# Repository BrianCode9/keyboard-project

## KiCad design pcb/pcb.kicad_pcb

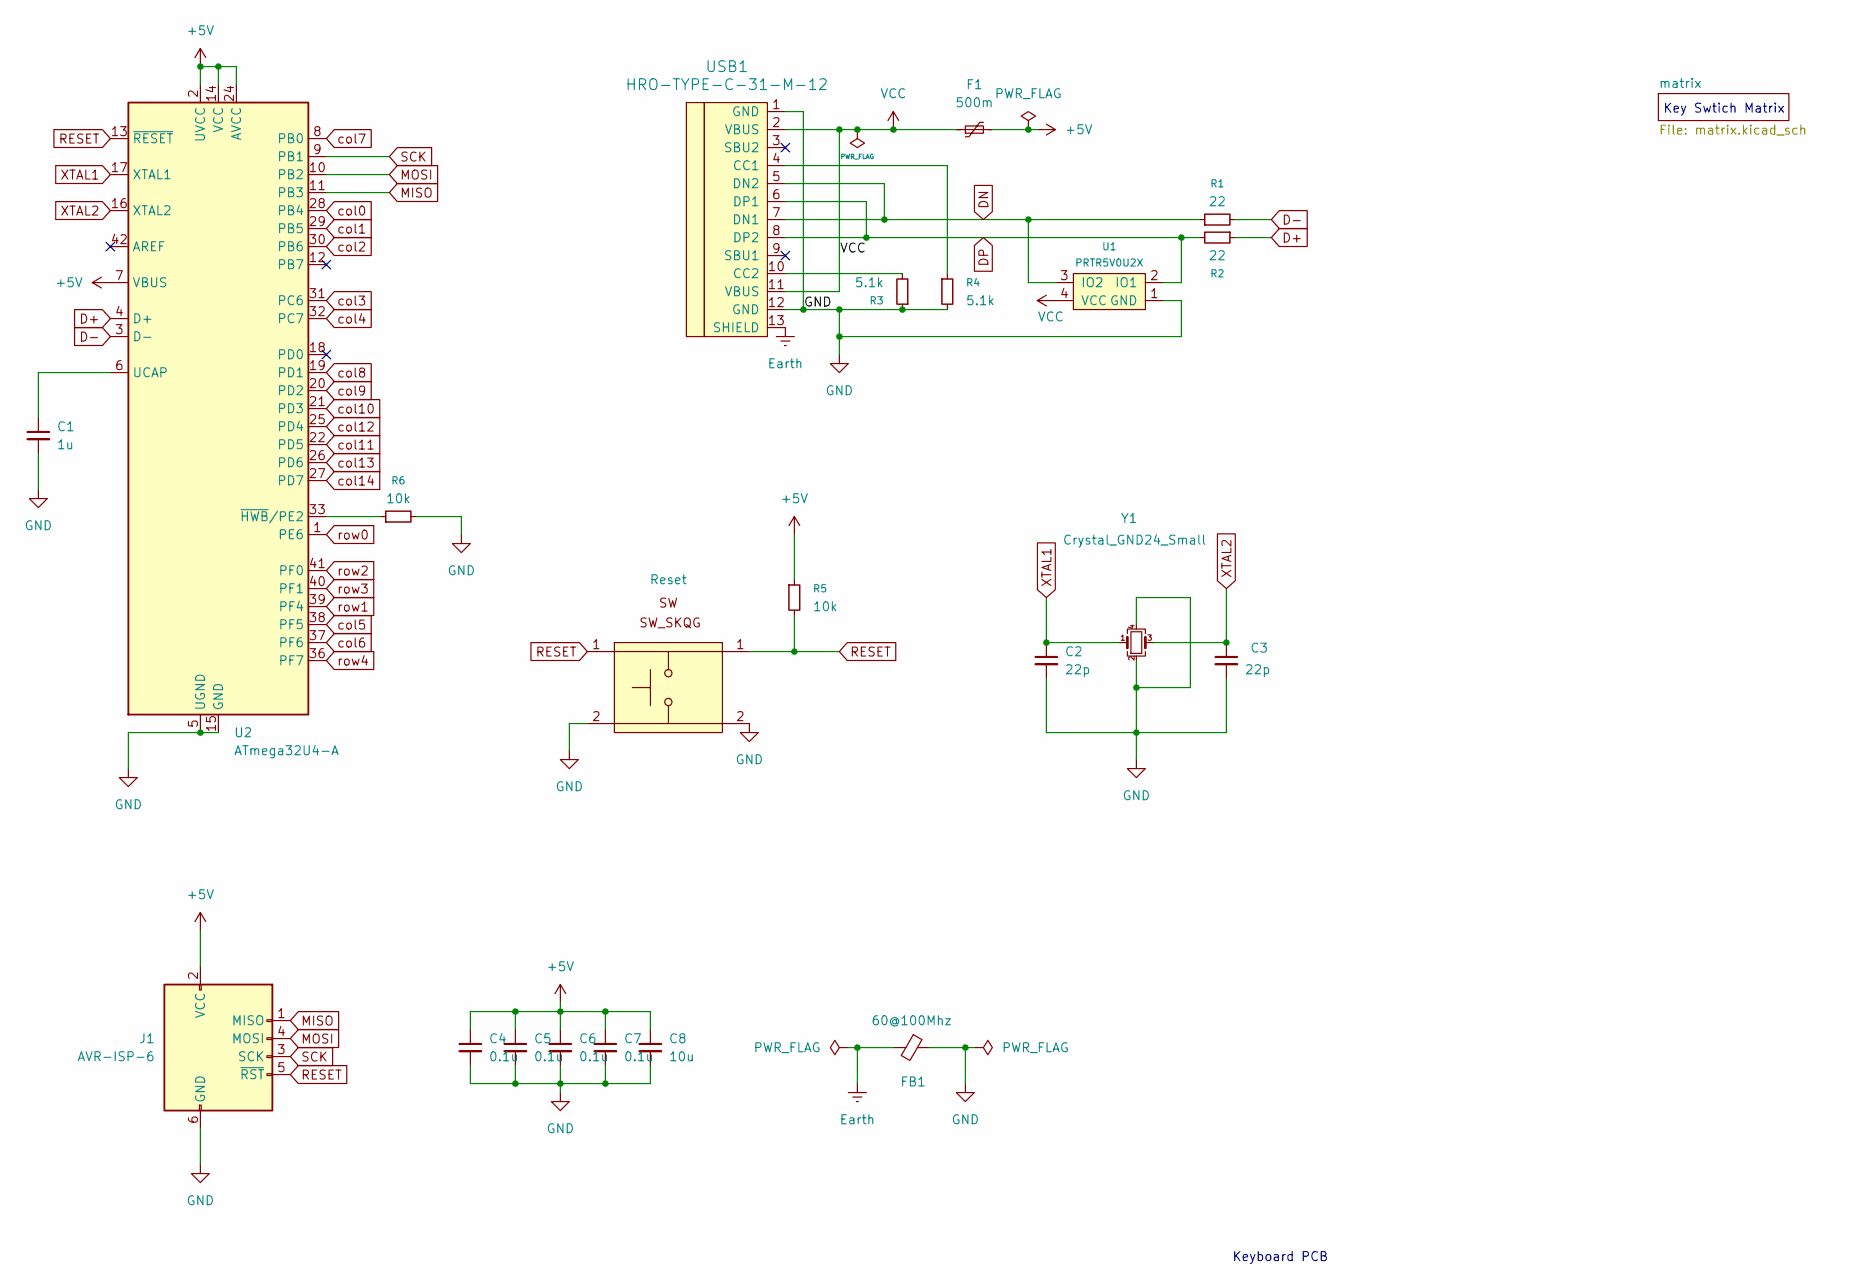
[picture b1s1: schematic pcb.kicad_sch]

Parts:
C1: 1u; C_0805_2012Metric_Pad1.18x1.45mm_HandSolder
C2, C3: 22p; C_0805_2012Metric_Pad1.18x1.45mm_HandSolder
C4, C5, C6, C7: 0.1u; C_0805_2012Metric_Pad1.18x1.45mm_HandSolder
C8: 10u; C_0805_2012Metric_Pad1.18x1.45mm_HandSolder
F1: 500m; Fuse_1206_3216Metric_Pad1.42x1.75mm_HandSolder
FB1: 60@100Mhz; L_0805_2012Metric_Pad1.05x1.20mm_HandSolder
J1: AVR-ISP-6; Reset_Pretty-Mask
R1, R2: 22; R_0805_2012Metric_Pad1.20x1.40mm_HandSolder
R3, R4: 5.1k; R_0805_2012Metric_Pad1.20x1.40mm_HandSolder
R5, R6: 10k; R_0805_2012Metric_Pad1.20x1.40mm_HandSolder
SW_RST1: Reset; SW_SPST_SKQG_WithStem
U1: PRTR5V0U2X; SOT143B
U2: ATmega32U4-A; TQFP-44_10x10mm_P0.8mm
USB1: HRO-TYPE-C-31-M-12; HRO-TYPE-C-31-M-12-HandSoldering
Y1: Crystal_GND24_Small; Crystal_SMD_3225-4Pin_3.2x2.5mm_HandSoldering

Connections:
+5V: C4.1, C5.1, C6.1, C7.1, C8.1, F1.2, J1.2 (VCC), R5.1, U2.2 (UVCC), U2.7 (VBUS), U2.14 (VCC), U2.24 (AVCC), U2.34 (VCC), U2.44 (AVCC)
D+: R2.1, U2.4 (D+)
D-: R1.2, U2.3 (D-)
DN: R1.1, U1.3 (IO2), USB1.5 (DN2), USB1.7 (DN1)
DP: R2.2, U1.2 (IO1), USB1.6 (DP1), USB1.8 (DP2)
Earth: FB1.2, USB1.13 (SHIELD)
GND: C1.2, C2.2, C3.2, C4.2, C5.2, C6.2, C7.2, C8.2, FB1.1, J1.6 (GND), R3.1, R4.2, R6.2, SW_RST1.2, U1.1 (GND), U2.5 (UGND), U2.15 (GND), U2.23 (GND), U2.35 (GND), U2.43 (GND), USB1.1 (GND), USB1.12 (GND), Y1.2, Y1.4
MISO: J1.1 (MISO), U2.11 (PB3)
MOSI: J1.4 (MOSI), U2.10 (PB2)
unnamed: C1.1, U2.6 (UCAP)
unnamed: R6.1, U2.33 (~HWB/PE2)
unnamed: R4.1, USB1.4 (CC1)
unnamed: R3.2, USB1.10 (CC2)
RESET: J1.5 (~RST), R5.2, SW_RST1.1, U2.13 (~RESET)
SCK: J1.3 (SCK), U2.9 (PB1)
VCC: F1.1, U1.4 (VCC), USB1.2 (VBUS), USB1.11 (VBUS)
XTAL1: C2.1, U2.17 (XTAL1), Y1.1
XTAL2: C3.1, U2.16 (XTAL2), Y1.3
col0: U2.28 (PB4); also elsewhere on the board
col1: U2.29 (PB5); also elsewhere on the board
col2: U2.30 (PB6); also elsewhere on the board
col3: U2.31 (PC6); also elsewhere on the board
col4: U2.32 (PC7); also elsewhere on the board
col5: U2.38 (PF5); also elsewhere on the board
col6: U2.37 (PF6); also elsewhere on the board
col7: U2.8 (PB0); also elsewhere on the board
col8: U2.19 (PD1); also elsewhere on the board
col9: U2.20 (PD2); also elsewhere on the board
col10: U2.21 (PD3); also elsewhere on the board
col11: U2.22 (PD5); also elsewhere on the board
col12: U2.25 (PD4); also elsewhere on the board
col13: U2.26 (PD6); also elsewhere on the board
col14: U2.27 (PD7); also elsewhere on the board
row0: U2.1 (PE6); also elsewhere on the board
row1: U2.39 (PF4); also elsewhere on the board
row2: U2.41 (PF0); also elsewhere on the board
row3: U2.40 (PF1); also elsewhere on the board
row4: U2.36 (PF7); also elsewhere on the board

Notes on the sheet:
Keyboard PCB
Key Swtich Matrix

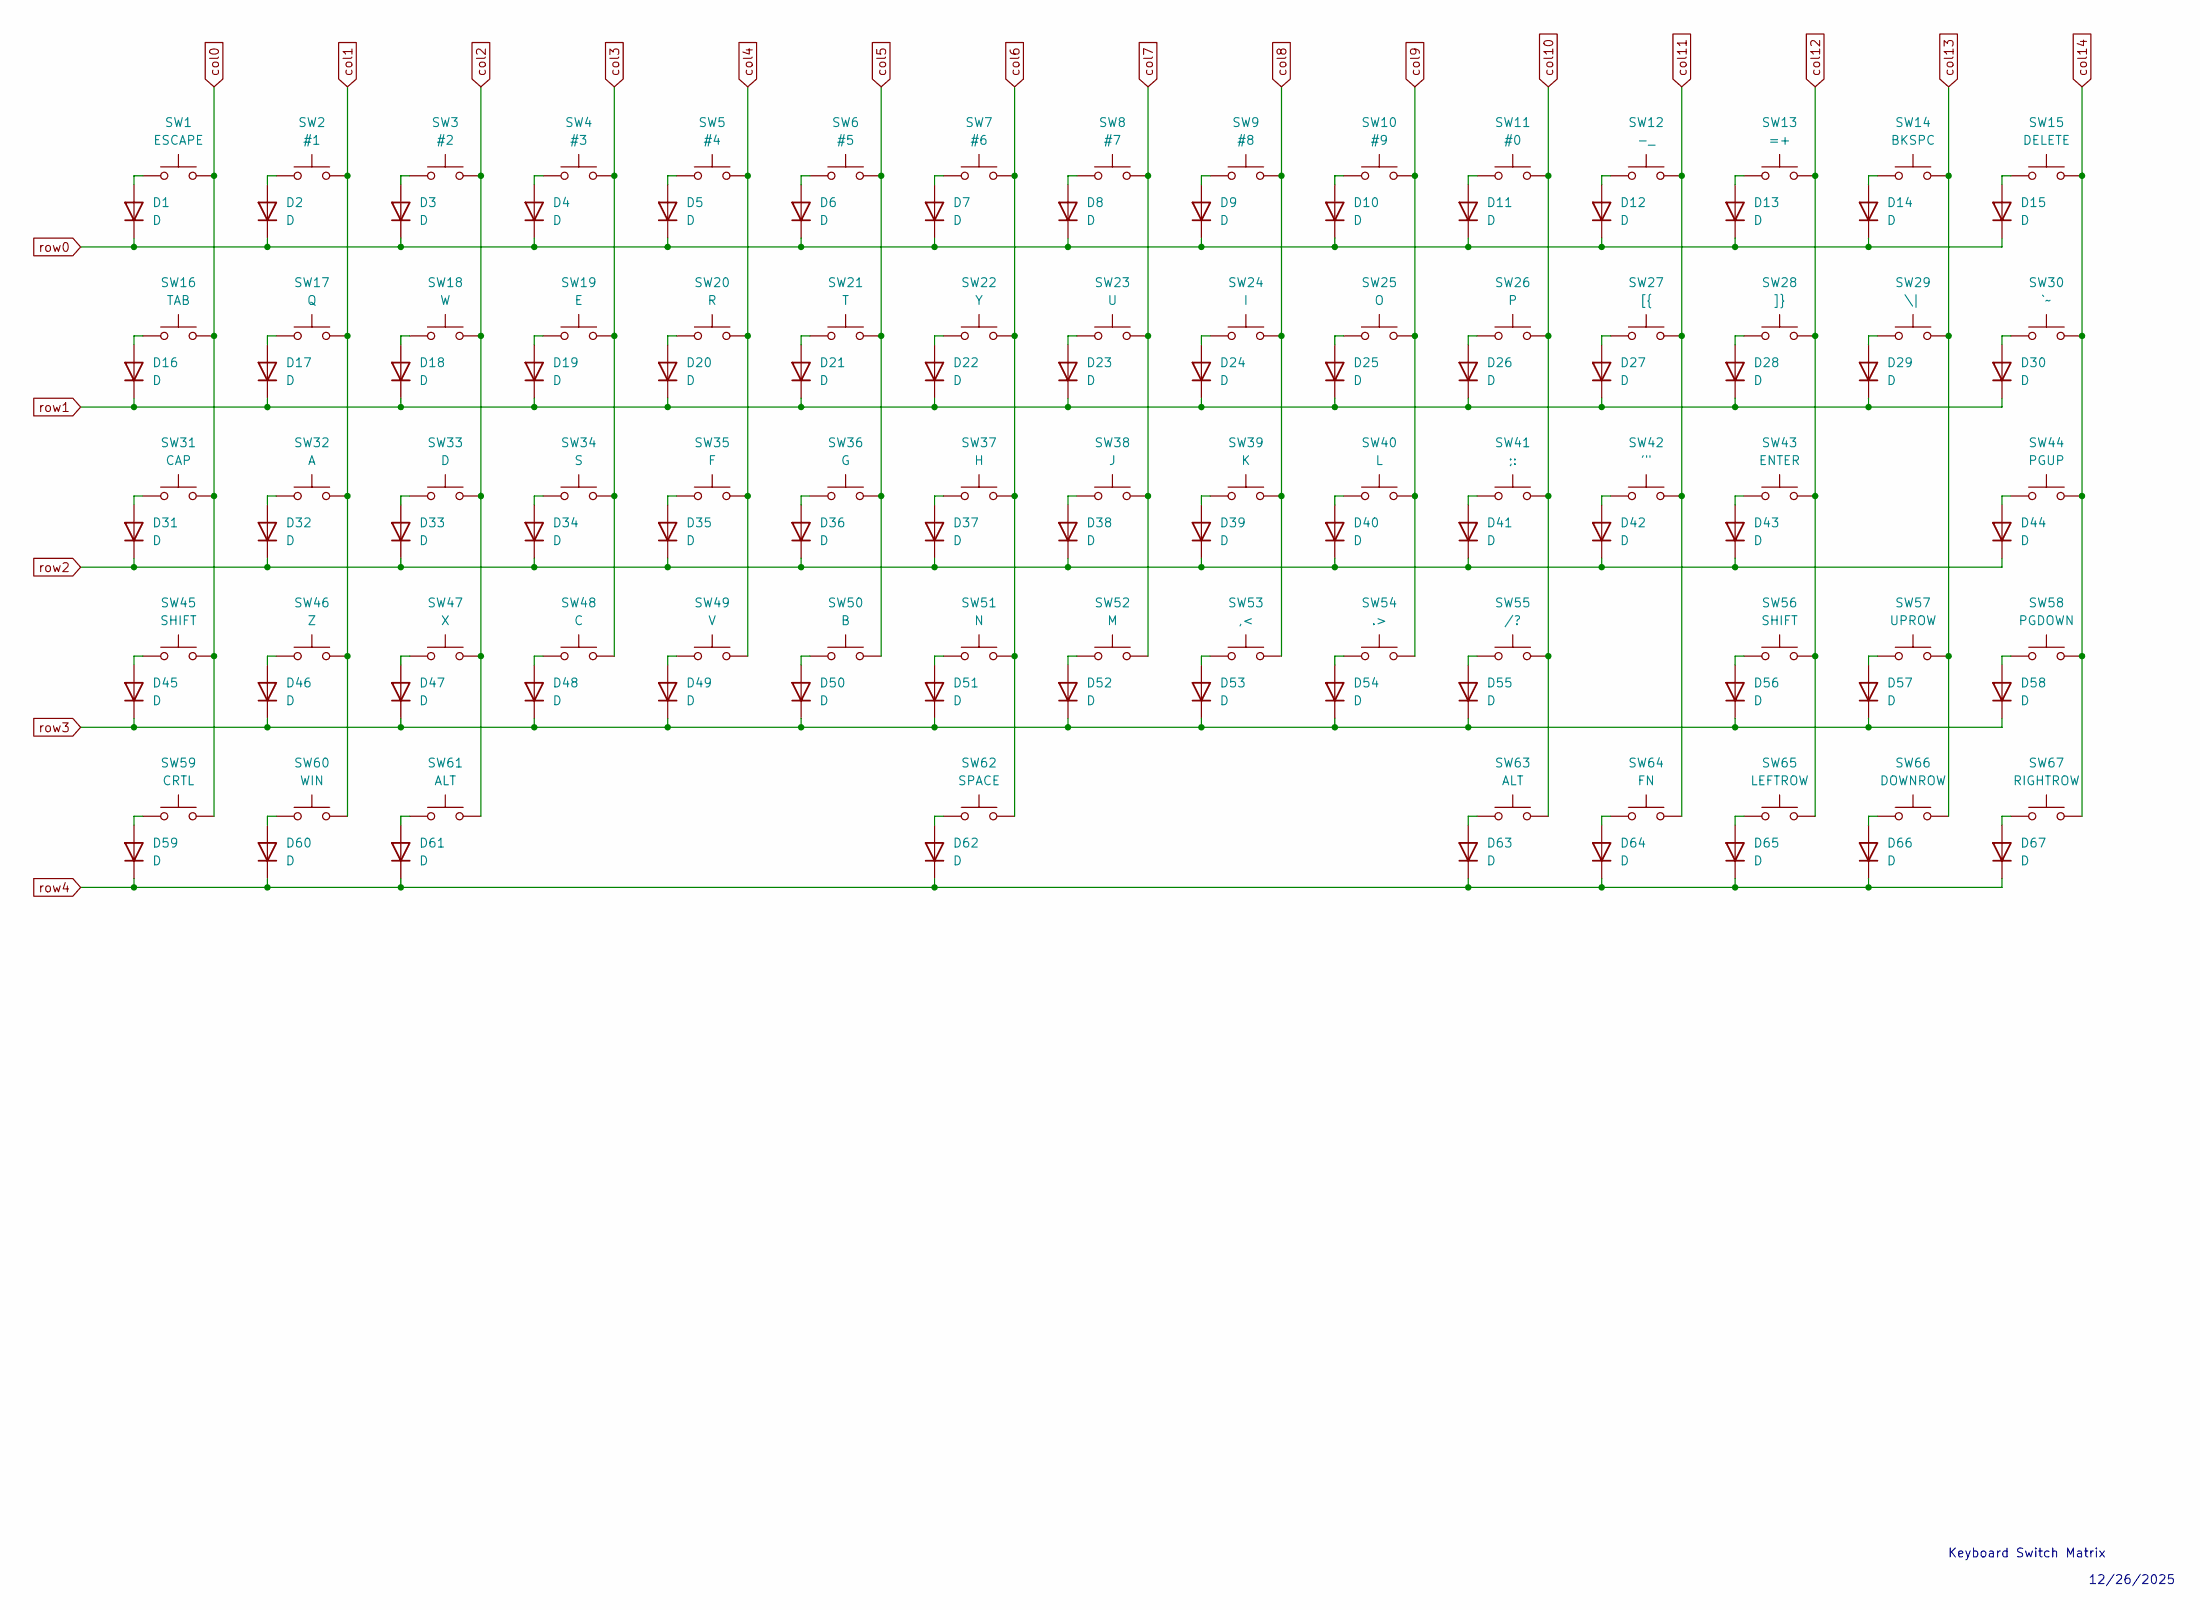
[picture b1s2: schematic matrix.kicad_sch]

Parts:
D1, D2, D3, D4, D5, D6, D7, D8, D9, D10, D11, D12, D13, D14, D15, D16, D17, D18, D19, D20, D21, D22, D23, D24, D25, D26, D27, D28, D29, D30, D31, D32, D33, D34, D35, D36, D37, D38, D39, D40, D41, D42, D43, D44, D45, D46, D47, D48, D49, D50, D51, D52, D53, D54, D55, D56, D57, D58, D59, D60, D61, D62, D63, D64, D65, D66, D67: D; D_SOD-123
SW1: ESCAPE; MXOnly-1U
SW2: #1; MXOnly-1U
SW3: #2; MXOnly-1U
SW4: #3; MXOnly-1U
SW5: #4; MXOnly-1U
SW6: #5; MXOnly-1U
SW7: #6; MXOnly-1U
SW8: #7; MXOnly-1U
SW9: #8; MXOnly-1U
SW10: #9; MXOnly-1U
SW11: #0; MXOnly-1U
SW12: -_; MXOnly-1U
SW13: =+; MXOnly-1U
SW14: BKSPC; MXOnly-2U
SW15: DELETE; MXOnly-1U
SW16: TAB; MXOnly-1.5U
SW17: Q; MXOnly-1U
SW18: W; MXOnly-1U
SW19: E; MXOnly-1U
SW20: R; MXOnly-1U
SW21: T; MXOnly-1U
SW22: Y; MXOnly-1U
SW23: U; MXOnly-1U
SW24: I; MXOnly-1U
SW25: O; MXOnly-1U
SW26: P; MXOnly-1U
SW27: [{; MXOnly-1U
SW28: ]}; MXOnly-1U
SW29: \|; MXOnly-1.5U
SW30: `~; MXOnly-1U
SW31: CAP; MXOnly-1.75U
SW32: A; MXOnly-1U
SW33: D; MXOnly-1U
SW34: S; MXOnly-1U
SW35: F; MXOnly-1U
SW36: G; MXOnly-1U
SW37: H; MXOnly-1U
SW38: J; MXOnly-1U
SW39: K; MXOnly-1U
SW40: L; MXOnly-1U
SW41: ;:; MXOnly-1U
SW42: '"; MXOnly-1U
SW43: ENTER; MXOnly-2.25U
SW44: PGUP; MXOnly-1U
SW45: SHIFT; MXOnly-2.25U
SW46: Z; MXOnly-1U
SW47: X; MXOnly-1U
SW48: C; MXOnly-1U
SW49: V; MXOnly-1U
SW50: B; MXOnly-1U
SW51: N; MXOnly-1U
SW52: M; MXOnly-1U
SW53: ,<; MXOnly-1U
SW54: .>; MXOnly-1U
SW55: /?; MXOnly-1U
SW56: SHIFT; MXOnly-1.75U
SW57: UPROW; MXOnly-1U
SW58: PGDOWN; MXOnly-1U
SW59: CRTL; MXOnly-1.75U
SW60: WIN; MXOnly-1.5U
SW61, SW63: ALT; MXOnly-1.25U
SW62: SPACE; MXOnly-6.25U
SW64: FN; MXOnly-1U
SW65: LEFTROW; MXOnly-1U
SW66: DOWNROW; MXOnly-1U
SW67: RIGHTROW; MXOnly-1U

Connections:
unnamed: D1.2 (A), SW1.1
unnamed: D2.2 (A), SW2.1
unnamed: D3.2 (A), SW3.1
unnamed: D4.2 (A), SW4.1
unnamed: D5.2 (A), SW5.1
unnamed: D6.2 (A), SW6.1
unnamed: D7.2 (A), SW7.1
unnamed: D8.2 (A), SW8.1
unnamed: D9.2 (A), SW9.1
unnamed: D10.2 (A), SW10.1
unnamed: D11.2 (A), SW11.1
unnamed: D12.2 (A), SW12.1
unnamed: D13.2 (A), SW13.1
unnamed: D14.2 (A), SW14.1
unnamed: D15.2 (A), SW15.1
unnamed: D16.2 (A), SW16.1
unnamed: D17.2 (A), SW17.1
unnamed: D18.2 (A), SW18.1
unnamed: D19.2 (A), SW19.1
unnamed: D20.2 (A), SW20.1
unnamed: D21.2 (A), SW21.1
unnamed: D22.2 (A), SW22.1
unnamed: D23.2 (A), SW23.1
unnamed: D24.2 (A), SW24.1
unnamed: D25.2 (A), SW25.1
unnamed: D26.2 (A), SW26.1
unnamed: D27.2 (A), SW27.1
unnamed: D28.2 (A), SW28.1
unnamed: D29.2 (A), SW29.1
unnamed: D30.2 (A), SW30.1
unnamed: D31.2 (A), SW31.1
unnamed: D32.2 (A), SW32.1
unnamed: D33.2 (A), SW33.1
unnamed: D34.2 (A), SW34.1
unnamed: D35.2 (A), SW35.1
unnamed: D36.2 (A), SW36.1
unnamed: D37.2 (A), SW37.1
unnamed: D38.2 (A), SW38.1
unnamed: D39.2 (A), SW39.1
unnamed: D40.2 (A), SW40.1
unnamed: D41.2 (A), SW41.1
unnamed: D42.2 (A), SW42.1
unnamed: D43.2 (A), SW43.1
unnamed: D44.2 (A), SW44.1
unnamed: D45.2 (A), SW45.1
unnamed: D46.2 (A), SW46.1
unnamed: D47.2 (A), SW47.1
unnamed: D48.2 (A), SW48.1
unnamed: D49.2 (A), SW49.1
unnamed: D50.2 (A), SW50.1
unnamed: D51.2 (A), SW51.1
unnamed: D52.2 (A), SW52.1
unnamed: D53.2 (A), SW53.1
unnamed: D54.2 (A), SW54.1
unnamed: D55.2 (A), SW55.1
unnamed: D56.2 (A), SW56.1
unnamed: D57.2 (A), SW57.1
unnamed: D58.2 (A), SW58.1
unnamed: D59.2 (A), SW59.1
unnamed: D60.2 (A), SW60.1
unnamed: D61.2 (A), SW61.1
unnamed: D62.2 (A), SW62.1
unnamed: D63.2 (A), SW63.1
unnamed: D64.2 (A), SW64.1
unnamed: D65.2 (A), SW65.1
unnamed: D66.2 (A), SW66.1
unnamed: D67.2 (A), SW67.1
col0: SW1.2, SW16.2, SW31.2, SW45.2, SW59.2; also elsewhere on the board
col1: SW2.2, SW17.2, SW32.2, SW46.2, SW60.2; also elsewhere on the board
col2: SW3.2, SW18.2, SW33.2, SW47.2, SW61.2; also elsewhere on the board
col3: SW4.2, SW19.2, SW34.2, SW48.2; also elsewhere on the board
col4: SW5.2, SW20.2, SW35.2, SW49.2; also elsewhere on the board
col5: SW6.2, SW21.2, SW36.2, SW50.2; also elsewhere on the board
col6: SW7.2, SW22.2, SW37.2, SW51.2, SW62.2; also elsewhere on the board
col7: SW8.2, SW23.2, SW38.2, SW52.2; also elsewhere on the board
col8: SW9.2, SW24.2, SW39.2, SW53.2; also elsewhere on the board
col9: SW10.2, SW25.2, SW40.2, SW54.2; also elsewhere on the board
col10: SW11.2, SW26.2, SW41.2, SW55.2, SW63.2; also elsewhere on the board
col11: SW12.2, SW27.2, SW42.2, SW64.2; also elsewhere on the board
col12: SW13.2, SW28.2, SW43.2, SW56.2, SW65.2; also elsewhere on the board
col13: SW14.2, SW29.2, SW57.2, SW66.2; also elsewhere on the board
col14: SW15.2, SW30.2, SW44.2, SW58.2, SW67.2; also elsewhere on the board
row0: D1.1 (K), D2.1 (K), D3.1 (K), D4.1 (K), D5.1 (K), D6.1 (K), D7.1 (K), D8.1 (K), D9.1 (K), D10.1 (K), D11.1 (K), D12.1 (K), D13.1 (K), D14.1 (K), D15.1 (K); also elsewhere on the board
row1: D16.1 (K), D17.1 (K), D18.1 (K), D19.1 (K), D20.1 (K), D21.1 (K), D22.1 (K), D23.1 (K), D24.1 (K), D25.1 (K), D26.1 (K), D27.1 (K), D28.1 (K), D29.1 (K), D30.1 (K); also elsewhere on the board
row2: D31.1 (K), D32.1 (K), D33.1 (K), D34.1 (K), D35.1 (K), D36.1 (K), D37.1 (K), D38.1 (K), D39.1 (K), D40.1 (K), D41.1 (K), D42.1 (K), D43.1 (K), D44.1 (K); also elsewhere on the board
row3: D45.1 (K), D46.1 (K), D47.1 (K), D48.1 (K), D49.1 (K), D50.1 (K), D51.1 (K), D52.1 (K), D53.1 (K), D54.1 (K), D55.1 (K), D56.1 (K), D57.1 (K), D58.1 (K); also elsewhere on the board
row4: D59.1 (K), D60.1 (K), D61.1 (K), D62.1 (K), D63.1 (K), D64.1 (K), D65.1 (K), D66.1 (K), D67.1 (K); also elsewhere on the board

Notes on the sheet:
12/26/2025
Keyboard Switch Matrix

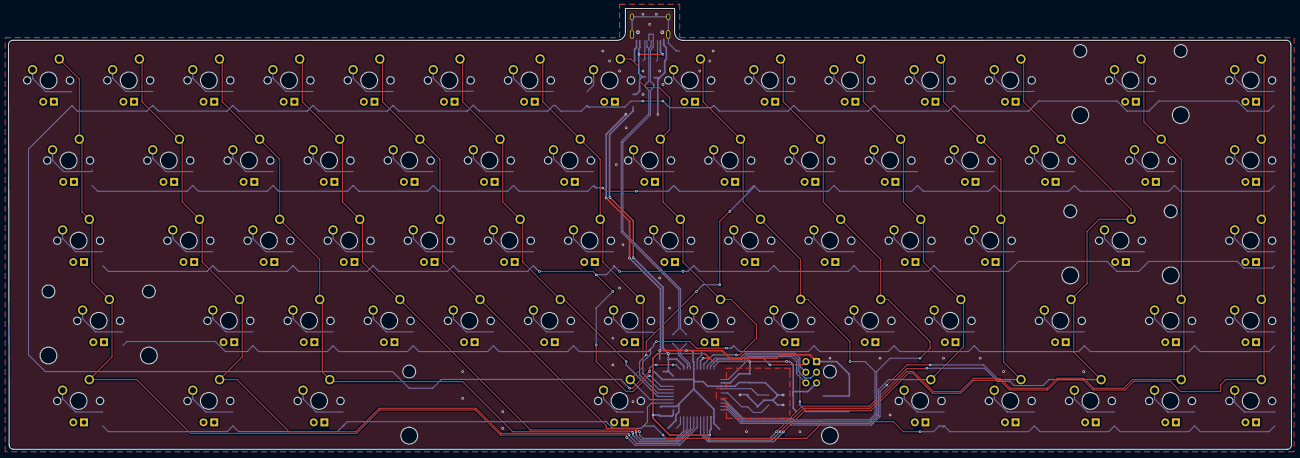
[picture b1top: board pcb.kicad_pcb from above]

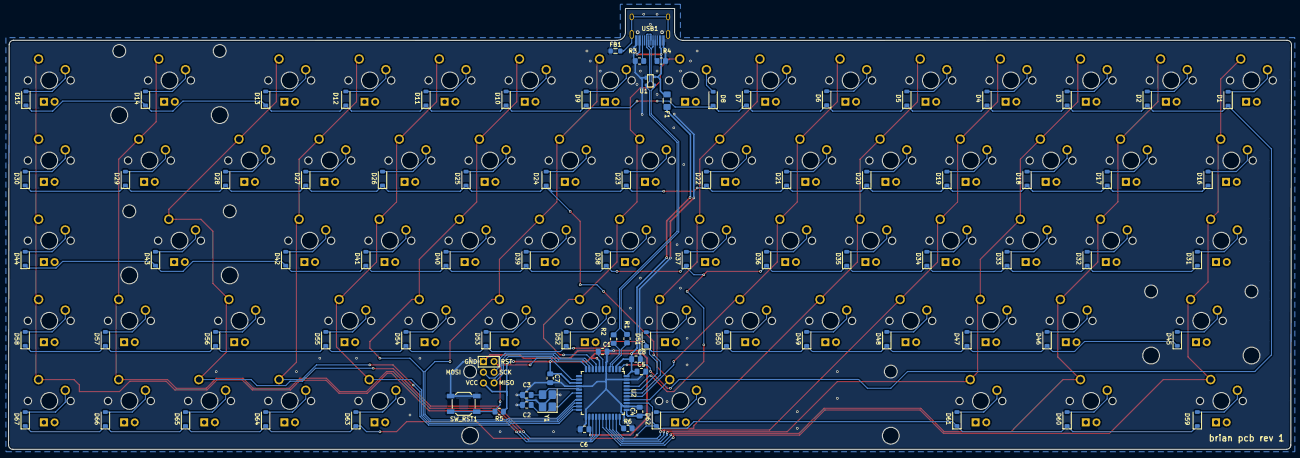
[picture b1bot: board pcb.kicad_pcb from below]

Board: 2 copper layers, 305.0 x 104.8 mm, 156 parts (89 on the bottom side), 105 nets.

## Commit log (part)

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2025-12-22 Kicad Project Initialization
2025-12-22 Added Kicad submodules
2025-12-22 Add Footprint Libraries
2025-12-22 Fixed mistake within Project Setup
    Changed the files to be in project specific libraries
2025-12-22 Setting Up Schematic Workspace
2025-12-23 More prep work
2025-12-24 Finished Zen Part 1
2025-12-25 Corrected Local Library
2025-12-26 Keyboard Switch Matrix Completed
2025-12-26 Saving Progress on Part 2
    Just started the footprint stuff for the switches. Need to make a decision on the switches I want for the keyboard.
2026-01-01 Footprints Finished
2026-01-01 Footprints Fix, Layout, and Diode Layout
    Fixed a spacing issue with the key switches. Made the control key bigger and then placed diodes. Now saving progress so that I can check that the connections made from the matrix schematic is correct.
2026-01-07 Keys and Diodes laid out
2026-01-15 Placement of all ICs Finished; Starting Error Checking
2026-01-16 Part 2 Fully Finished
2026-01-21 Saving Progress on Part 3
